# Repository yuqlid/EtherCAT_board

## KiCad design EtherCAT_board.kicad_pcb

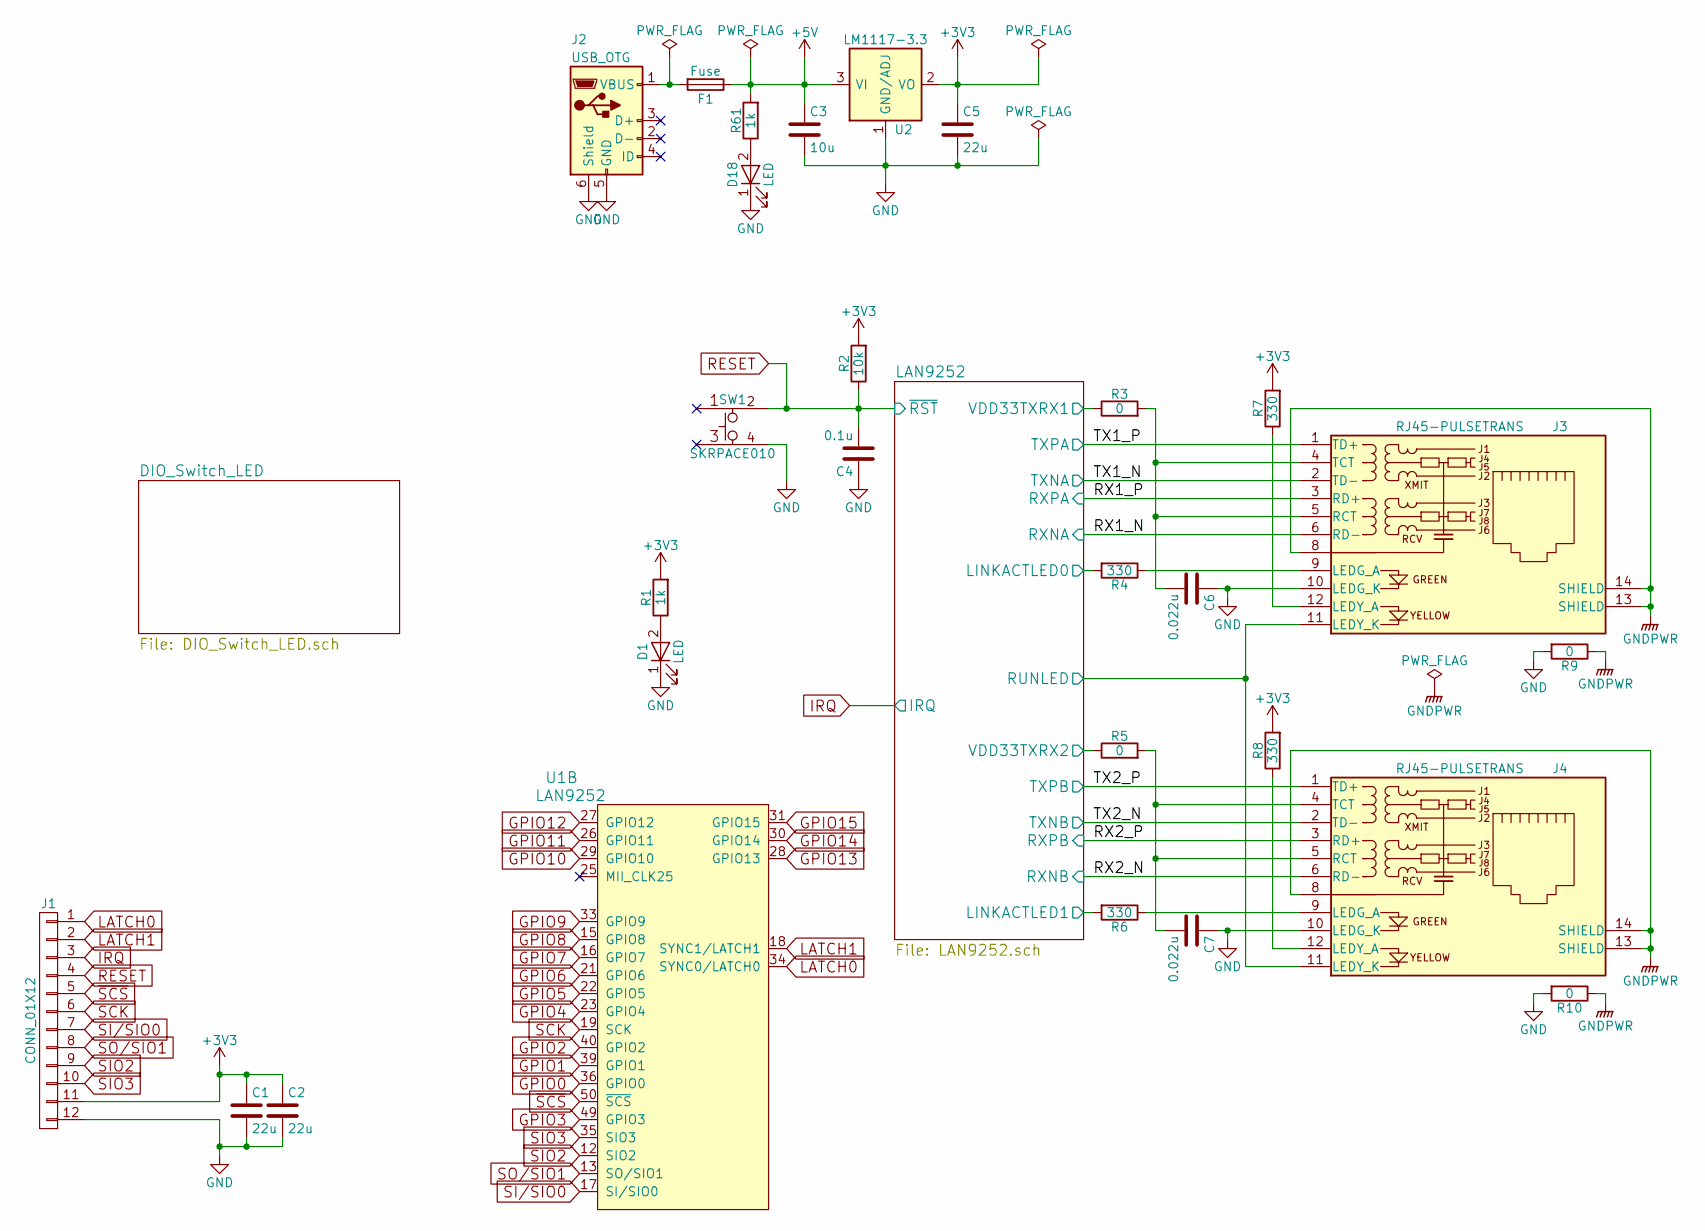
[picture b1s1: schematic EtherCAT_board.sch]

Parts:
C1, C2, C5: 22u; C_0603
C3: 10u; C_0603
C4: 0.1u; C_0603
C6, C7: 0.022u; C_0603
D1, D18: LED; LED_0603
F1: Fuse; R_1210
J1: CONN_01X12; Pin_Header_Straight_1x12_Pitch2.54mm
J2: USB_OTG; USB_Micro-B
J3, J4: RJ45-PULSETRANS; RJ45_J0011D21BNL
R1, R61: 1k; R_0603
R2: 10k; R_0603
R3, R5: 0; R_0603
R4, R6, R7, R8: 330; R_0603
R9, R10: 0; R_1210
SW1: SKRPACE010; ALPS_SKRPAxE010
U1: LAN9252; QFN-64-1EP_9x9mm_Pitch0.5mm_LAN9252
U2: LM1117-3.3; SOT-223-3Lead_TabPin2

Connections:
+3V3: C1.1, C2.1, C5.1, J1.11, R1.2, R2.2, R7.2, R8.2, U2.2 (VO), U2.4 (VO); also elsewhere on the board
+5V: C3.1, F1.1, R61.2, U2.3 (VI)
/LAN9252/LINKACTLED0: R4.2; also elsewhere on the board
/LAN9252/LINKACTLED1: R6.2; also elsewhere on the board
/LAN9252/RUNLED: J3.11 (LEDY_K), J4.11 (LEDY_K); also elsewhere on the board
/LAN9252/VDD33TXRX1: R3.1; also elsewhere on the board
/LAN9252/VDD33TXRX2: R5.1; also elsewhere on the board
/RX1_N: J3.6 (RD-); also elsewhere on the board
/RX1_P: J3.3 (RD+); also elsewhere on the board
/RX2_N: J4.6 (RD-); also elsewhere on the board
/RX2_P: J4.3 (RD+); also elsewhere on the board
/TX1_N: J3.2 (TD-); also elsewhere on the board
/TX1_P: J3.1 (TD+); also elsewhere on the board
/TX2_N: J4.2 (TD-); also elsewhere on the board
/TX2_P: J4.1 (TD+); also elsewhere on the board
GND: C1.2, C2.2, C3.2, C4.1, C5.2, C6.1, C7.1, D1.1 (K), D18.1 (K), J1.12, J2.5 (GND), J2.6 (Shield), J3.10 (LEDG_K), J4.10 (LEDG_K), R9.2, R10.2, SW1.4, U2.1 (GND/ADJ); also elsewhere on the board
GNDPWR: J3.8, J3.13 (SHIELD), J3.14 (SHIELD), J4.8, J4.13 (SHIELD), J4.14 (SHIELD), R9.1, R10.1
GPIO0: U1.36 (GPIO0); also elsewhere on the board
GPIO1: U1.39 (GPIO1); also elsewhere on the board
GPIO2: U1.40 (GPIO2); also elsewhere on the board
GPIO3: U1.49 (GPIO3); also elsewhere on the board
GPIO4: U1.23 (GPIO4); also elsewhere on the board
GPIO5: U1.22 (GPIO5); also elsewhere on the board
GPIO6: U1.21 (GPIO6); also elsewhere on the board
GPIO7: U1.16 (GPIO7); also elsewhere on the board
GPIO8: U1.15 (GPIO8); also elsewhere on the board
GPIO9: U1.33 (GPIO9); also elsewhere on the board
GPIO10: U1.29 (GPIO10); also elsewhere on the board
GPIO11: U1.26 (GPIO11); also elsewhere on the board
GPIO12: U1.27 (GPIO12); also elsewhere on the board
GPIO13: U1.28 (GPIO13); also elsewhere on the board
GPIO14: U1.30 (GPIO14); also elsewhere on the board
GPIO15: U1.31 (GPIO15); also elsewhere on the board
IRQ: J1.3; also elsewhere on the board
LATCH0: J1.1, U1.34 (SYNC0/LATCH0)
LATCH1: J1.2, U1.18 (SYNC1/LATCH1)
unnamed: C6.2, J3.4 (TCT), J3.5 (RCT), R3.2
unnamed: C7.2, J4.4 (TCT), J4.5 (RCT), R5.2
unnamed: D1.2 (A), R1.1
unnamed: D18.2 (A), R61.1
unnamed: F1.2, J2.1 (VBUS)
unnamed: J3.9 (LEDG_A), R4.1
unnamed: J3.12 (LEDY_A), R7.1
unnamed: J4.9 (LEDG_A), R6.1
unnamed: J4.12 (LEDY_A), R8.1
RESET: C4.2, J1.4, R2.1, SW1.2; also elsewhere on the board
SCK: J1.6, U1.19 (SCK)
SI/SIO0: J1.7, U1.17 (SI/SIO0)
SIO2: J1.9, U1.12 (SIO2)
SIO3: J1.10, U1.35 (SIO3)
SO/SIO1: J1.8, U1.13 (SO/SIO1)
~SCS: J1.5, U1.50 (~SCS)

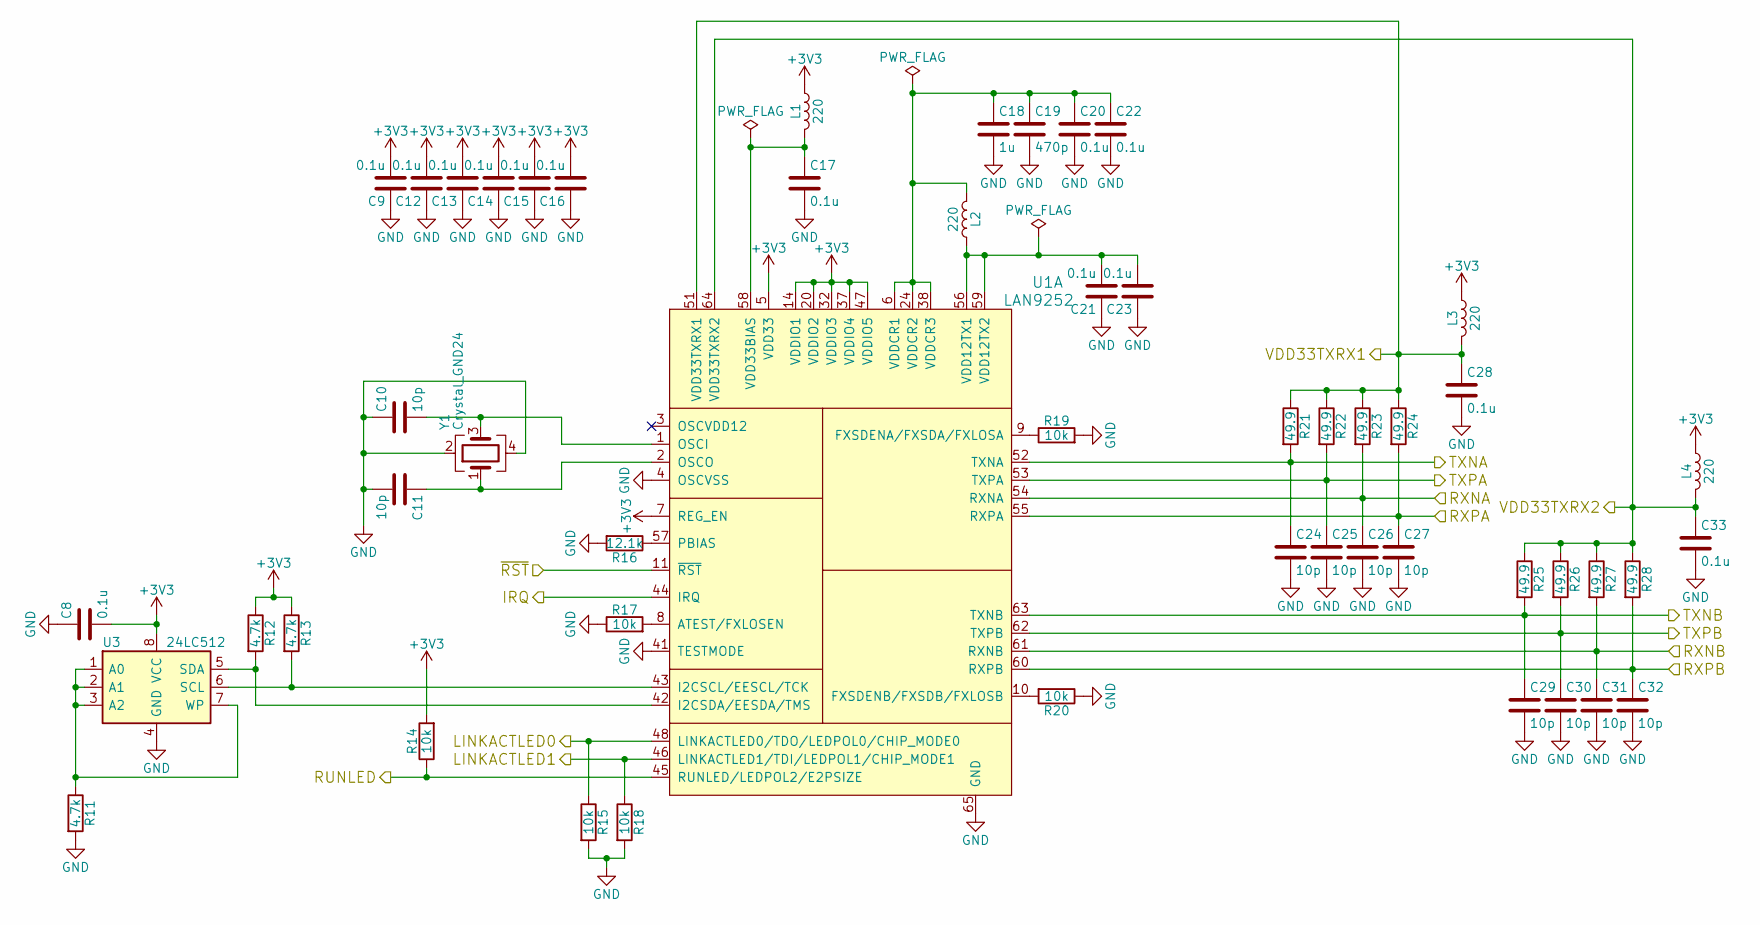
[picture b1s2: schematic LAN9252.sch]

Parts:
C8, C9, C12, C13, C14, C15, C16, C17, C20, C21, C22, C23, C28, C33: 0.1u; C_0603
C10, C11, C24, C25, C26, C27, C29, C30, C31, C32: 10p; C_0603
C18: 1u; C_0603
C19: 470p; C_0603
L1, L2, L3, L4: 220; C_0603
R11, R12, R13: 4.7k; R_0603
R14, R15, R17, R18, R19, R20: 10k; R_0603
R16: 12.1k; R_0603
R21, R22, R23, R24, R25, R26, R27, R28: 49.9; R_0603
U1: LAN9252; QFN-64-1EP_9x9mm_Pitch0.5mm_LAN9252
U3: 24LC512; SOIC-8_3.9x4.9mm_Pitch1.27mm
Y1: Crystal_GND24; Crystal_SMD_Abracon_ABM8G-4pin_3.2x2.5mm

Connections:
+3V3: C8.2, C9.2, C12.2, C13.2, C14.2, C15.2, C16.2, L1.1, L3.1, L4.1, R12.1, R13.1, R14.2, U1.5 (VDD33), U1.7 (REG_EN), U1.14 (VDDIO1), U1.20 (VDDIO2), U1.32 (VDDIO3), U1.37 (VDDIO4), U1.47 (VDDIO5), U3.8 (VCC); also elsewhere on the board
/LAN9252/LINKACTLED0: R15.1, U1.48 (LINKACTLED0/TDO/LEDPOL0/CHIP_MODE0); also elsewhere on the board
/LAN9252/LINKACTLED1: R18.1, U1.46 (LINKACTLED1/TDI/LEDPOL1/CHIP_MODE1); also elsewhere on the board
/LAN9252/RUNLED: R14.1, U1.45 (RUNLED/LEDPOL2/E2PSIZE); also elsewhere on the board
/LAN9252/VDD33TXRX1: C28.1, L3.2, R21.1, R22.1, R23.1, R24.1, U1.51 (VDD33TXRX1); also elsewhere on the board
/LAN9252/VDD33TXRX2: C33.1, L4.2, R25.1, R26.1, R27.1, R28.1, U1.64 (VDD33TXRX2); also elsewhere on the board
/RX1_N: C26.1, R23.2, U1.54 (RXNA); also elsewhere on the board
/RX1_P: C27.1, R24.2, U1.55 (RXPA); also elsewhere on the board
/RX2_N: C31.1, R27.2, U1.61 (RXNB); also elsewhere on the board
/RX2_P: C32.1, R28.2, U1.60 (RXPB); also elsewhere on the board
/TX1_N: C24.1, R21.2, U1.52 (TXNA); also elsewhere on the board
/TX1_P: C25.1, R22.2, U1.53 (TXPA); also elsewhere on the board
/TX2_N: C29.1, R25.2, U1.63 (TXNB); also elsewhere on the board
/TX2_P: C30.1, R26.2, U1.62 (TXPB); also elsewhere on the board
GND: C8.1, C9.1, C10.1, C11.2, C12.1, C13.1, C14.1, C15.1, C16.1, C17.2, C18.2, C19.2, C20.2, C21.1, C22.2, C23.1, C24.2, C25.2, C26.2, C27.2, C28.2, C29.2, C30.2, C31.2, C32.2, C33.2, R11.2, R15.2, R16.2, R17.1, R18.2, R19.2, R20.1, U1.4 (OSCVSS), U1.41 (TESTMODE), U1.65 (GND), U3.4 (GND), Y1.2, Y1.4; also elsewhere on the board
IRQ: U1.44 (IRQ); also elsewhere on the board
unnamed: C10.2, U1.1 (OSCI), Y1.3
unnamed: C11.1, U1.2 (OSCO), Y1.1
unnamed: C17.1, L1.2, U1.58 (VDD33BIAS)
unnamed: C18.1, C19.1, C20.1, C22.1, L2.2, U1.6 (VDDCR1), U1.24 (VDDCR2), U1.38 (VDDCR3)
unnamed: C21.2, C23.2, L2.1, U1.56 (VDD12TX1), U1.59 (VDD12TX2)
unnamed: R11.1, U3.1 (A0), U3.2 (A1), U3.3 (A2), U3.7 (WP)
unnamed: R12.2, U1.42 (I2CSDA/EESDA/TMS), U3.5 (SDA)
unnamed: R13.2, U1.43 (I2CSCL/EESCL/TCK), U3.6 (SCL)
unnamed: R16.1, U1.57 (PBIAS)
unnamed: R17.2, U1.8 (ATEST/FXLOSEN)
unnamed: R19.1, U1.9 (FXSDENA/FXSDA/FXLOSA)
unnamed: R20.2, U1.10 (FXSDENB/FXSDB/FXLOSB)
RESET: U1.11 (~RST); also elsewhere on the board

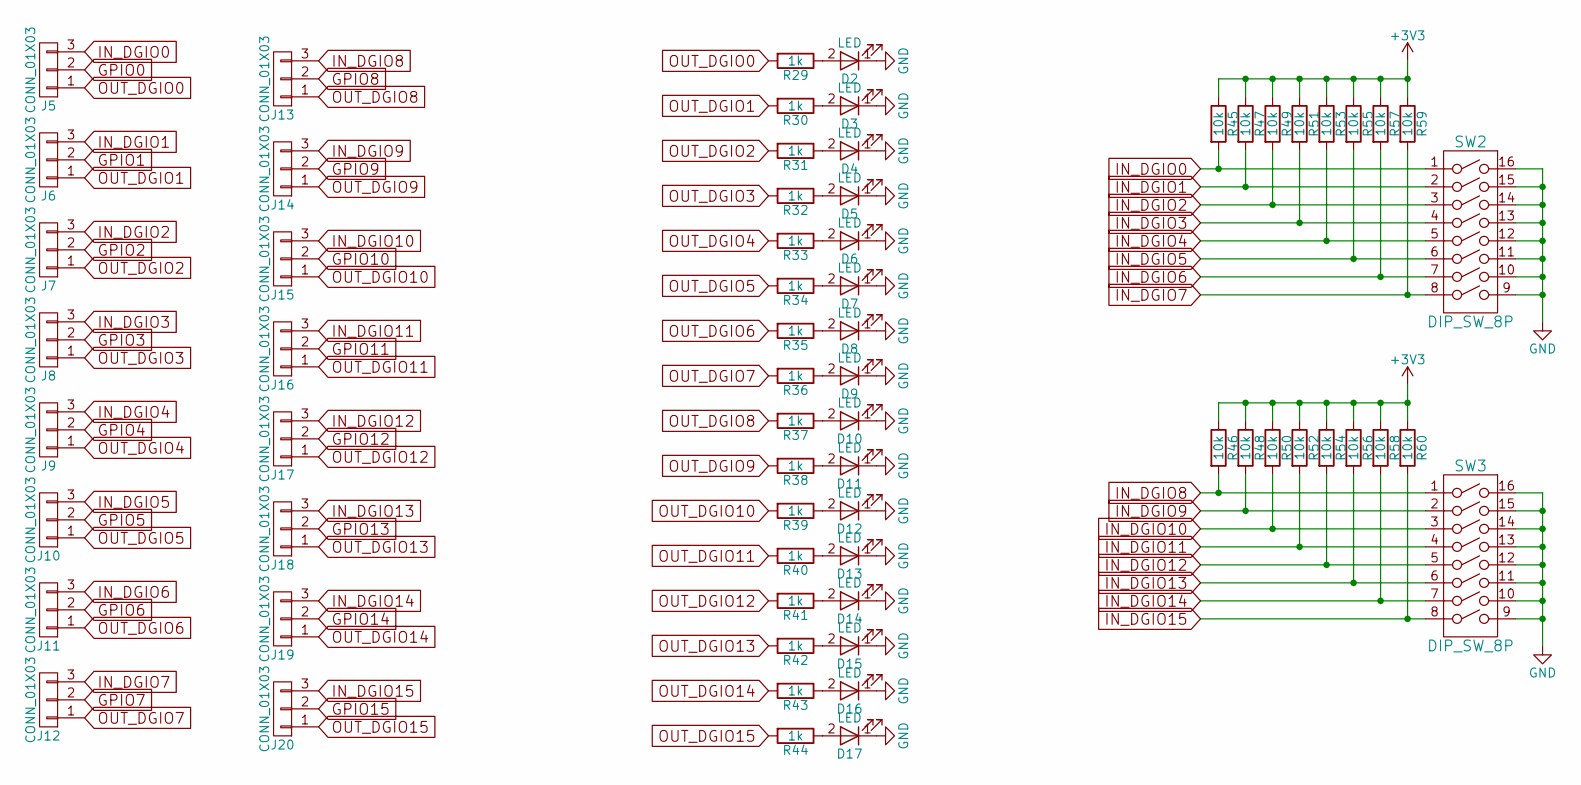
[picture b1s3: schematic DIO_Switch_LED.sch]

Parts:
D2, D3, D4, D5, D6, D7, D8, D9, D10, D11, D12, D13, D14, D15, D16, D17: LED; LED_0603
J5, J6, J7, J8, J9, J10, J11, J12, J13, J14, J15, J16, J17, J18, J19, J20: CONN_01X03; Pin_Header_Straight_1x03_Pitch2.54mm
R29, R30, R31, R32, R33, R34, R35, R36, R37, R38, R39, R40, R41, R42, R43, R44: 1k; R_0603
R45, R46, R47, R48, R49, R50, R51, R52, R53, R54, R55, R56, R57, R58, R59, R60: 10k; R_0603
SW2, SW3: DIP_SW_8P; SW_DIP_x8_W7.62mm_Slide

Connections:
+3V3: R45.1, R46.1, R47.1, R48.1, R49.1, R50.1, R51.1, R52.1, R53.1, R54.1, R55.1, R56.1, R57.1, R58.1, R59.1, R60.1; also elsewhere on the board
GND: D2.1 (K), D3.1 (K), D4.1 (K), D5.1 (K), D6.1 (K), D7.1 (K), D8.1 (K), D9.1 (K), D10.1 (K), D11.1 (K), D12.1 (K), D13.1 (K), D14.1 (K), D15.1 (K), D16.1 (K), D17.1 (K), SW2.9, SW2.10, SW2.11, SW2.12, SW2.13, SW2.14, SW2.15, SW2.16, SW3.9, SW3.10, SW3.11, SW3.12, SW3.13, SW3.14, SW3.15, SW3.16; also elsewhere on the board
GPIO0: J5.2; also elsewhere on the board
GPIO1: J6.2; also elsewhere on the board
GPIO2: J7.2; also elsewhere on the board
GPIO3: J8.2; also elsewhere on the board
GPIO4: J9.2; also elsewhere on the board
GPIO5: J10.2; also elsewhere on the board
GPIO6: J11.2; also elsewhere on the board
GPIO7: J12.2; also elsewhere on the board
GPIO8: J13.2; also elsewhere on the board
GPIO9: J14.2; also elsewhere on the board
GPIO10: J15.2; also elsewhere on the board
GPIO11: J16.2; also elsewhere on the board
GPIO12: J17.2; also elsewhere on the board
GPIO13: J18.2; also elsewhere on the board
GPIO14: J19.2; also elsewhere on the board
GPIO15: J20.2; also elsewhere on the board
IN_DGIO0: J5.3, R45.2, SW2.1
IN_DGIO1: J6.3, R47.2, SW2.2
IN_DGIO2: J7.3, R49.2, SW2.3
IN_DGIO3: J8.3, R51.2, SW2.4
IN_DGIO4: J9.3, R53.2, SW2.5
IN_DGIO5: J10.3, R55.2, SW2.6
IN_DGIO6: J11.3, R57.2, SW2.7
IN_DGIO7: J12.3, R59.2, SW2.8
IN_DGIO8: J13.3, R46.2, SW3.1
IN_DGIO9: J14.3, R48.2, SW3.2
IN_DGIO10: J15.3, R50.2, SW3.3
IN_DGIO11: J16.3, R52.2, SW3.4
IN_DGIO12: J17.3, R54.2, SW3.5
IN_DGIO13: J18.3, R56.2, SW3.6
IN_DGIO14: J19.3, R58.2, SW3.7
IN_DGIO15: J20.3, R60.2, SW3.8
unnamed: D2.2 (A), R29.1
unnamed: D3.2 (A), R30.1
unnamed: D4.2 (A), R31.1
unnamed: D5.2 (A), R32.1
unnamed: D6.2 (A), R33.1
unnamed: D7.2 (A), R34.1
unnamed: D8.2 (A), R35.1
unnamed: D9.2 (A), R36.1
unnamed: D10.2 (A), R37.1
unnamed: D11.2 (A), R38.1
unnamed: D12.2 (A), R39.1
unnamed: D13.2 (A), R40.1
unnamed: D14.2 (A), R41.1
unnamed: D15.2 (A), R42.1
unnamed: D16.2 (A), R43.1
unnamed: D17.2 (A), R44.1
OUT_DGIO0: J5.1, R29.2
OUT_DGIO1: J6.1, R30.2
OUT_DGIO2: J7.1, R31.2
OUT_DGIO3: J8.1, R32.2
OUT_DGIO4: J9.1, R33.2
OUT_DGIO5: J10.1, R34.2
OUT_DGIO6: J11.1, R35.2
OUT_DGIO7: J12.1, R36.2
OUT_DGIO8: J13.1, R37.2
OUT_DGIO9: J14.1, R38.2
OUT_DGIO10: J15.1, R39.2
OUT_DGIO11: J16.1, R40.2
OUT_DGIO12: J17.1, R41.2
OUT_DGIO13: J18.1, R42.2
OUT_DGIO14: J19.1, R43.2
OUT_DGIO15: J20.1, R44.2

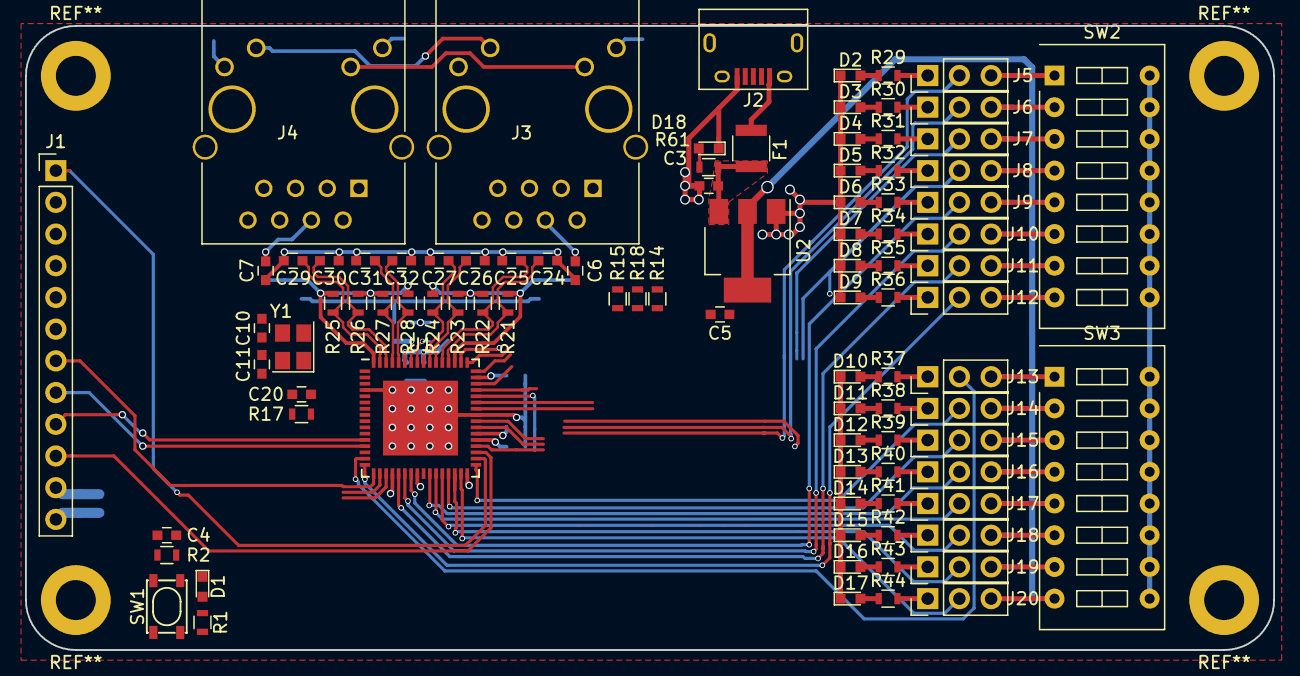
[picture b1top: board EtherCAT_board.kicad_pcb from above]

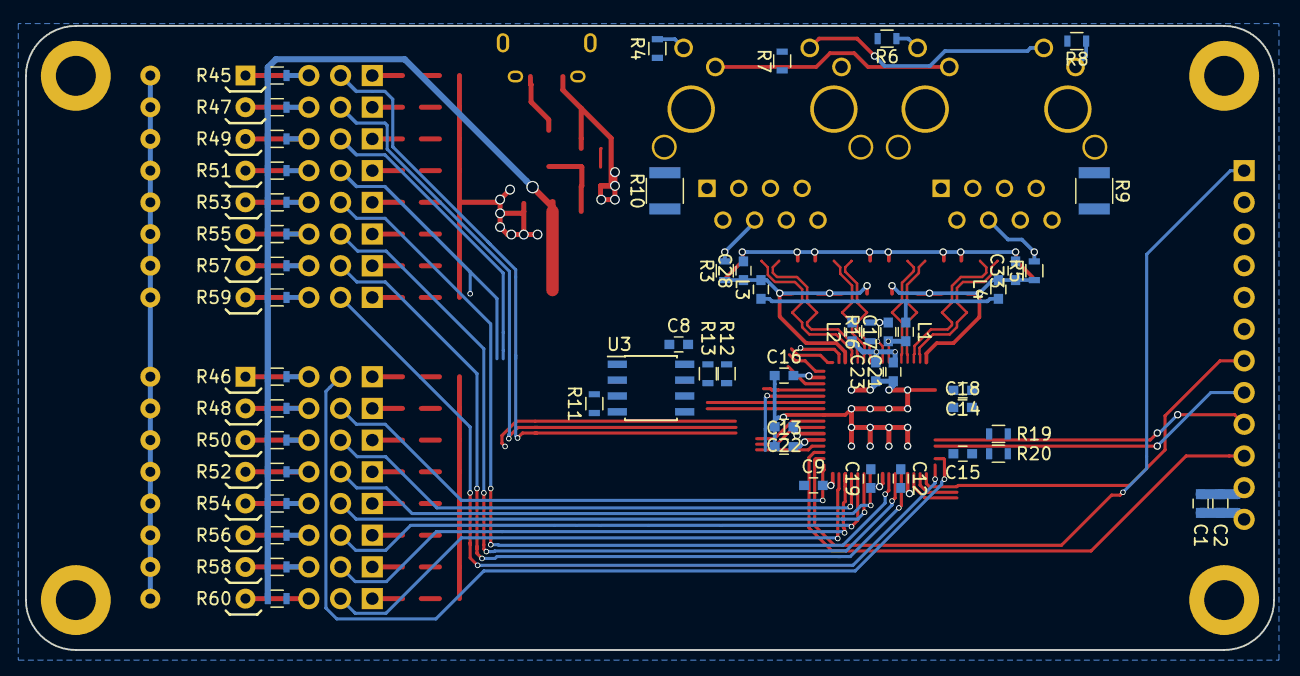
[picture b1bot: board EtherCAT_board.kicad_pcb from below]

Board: 2 copper layers, 100.0 x 50.0 mm, 144 parts (52 on the bottom side), 112 nets.

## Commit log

2017-05-20 Add kicad project
2017-05-21 Add library file to project
2017-05-21 Add new sheet LAN9252
2017-05-22 LAN9252まわりの配線した
2017-05-24 スイッチ，LEDの配線 電源回路追加 アノテーション
2017-05-24 フットプリント割当 基板作成開始
2017-05-24 GPIO周りをまとめた
2017-05-24 基板内に部品を納めた
2017-05-26 GPIOまわりを配線
2017-05-28 5Vの電源LEDを追加 ポリスイッチのサイズを3225に変更
2017-06-27 Create LICENSE
